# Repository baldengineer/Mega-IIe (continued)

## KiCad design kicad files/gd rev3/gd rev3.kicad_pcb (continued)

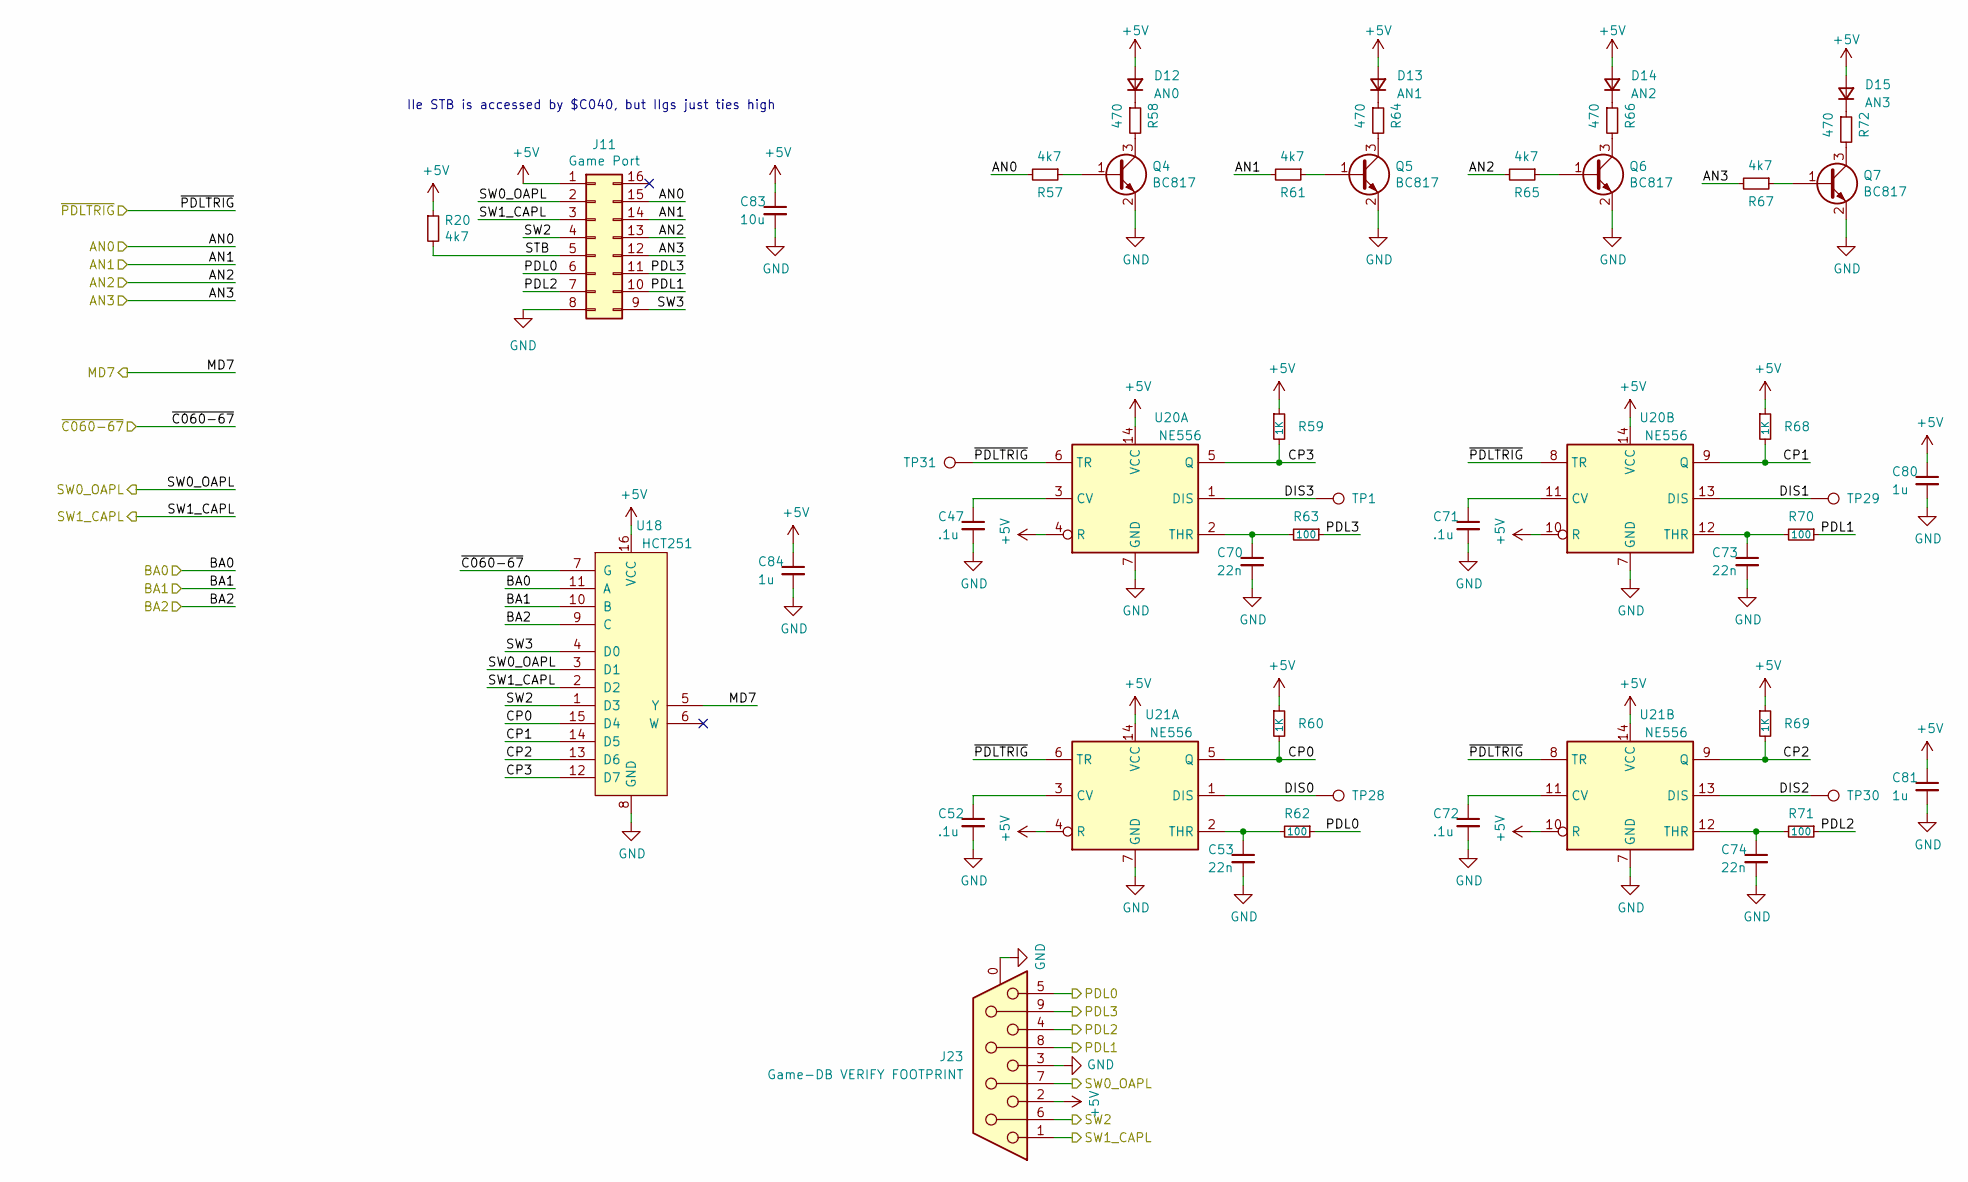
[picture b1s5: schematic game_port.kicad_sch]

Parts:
C47, C52, C71, C72: .1u; C_0805_2012Metric
C53, C70, C73, C74: 22n; C_0805_2012Metric
C80, C81, C84: 1u; C_0805_2012Metric
C83: 10u; C_0805_2012Metric
D12: AN0; LED_1206_3216Metric
D13: AN1; LED_1206_3216Metric
D14: AN2; LED_1206_3216Metric
D15: AN3; LED_1206_3216Metric
J11: Game Port; DIP-16_W7.62mm_Socket
J23: Game-DB VERIFY FOOTPRINT; DSUB-9_Female_Horizontal_P2.77x2.84mm_EdgePinOffset4.94mm_H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
Q4, Q5, Q6, Q7: BC817; SOT-23
R20, R57, R61, R65, R67: 4k7; R_0805_2012Metric
R58, R64, R66, R72: 470; R_0805_2012Metric
R59, R60, R68, R69: 1K; R_0805_2012Metric
R62, R63, R70, R71: 100; R_0805_2012Metric
TP1, TP28, TP29, TP30, TP31: TestPoint; TestPoint_Pad_D1.0mm
U18: HCT251; SOIC-16_3.9x9.9mm_P1.27mm; MPN 74HCT251D,652
U20, U21: NE556; SO-14_3.9x8.65mm_P1.27mm

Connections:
/IWM/BA0: U18.11 (A); also elsewhere on the board
/IWM/BA1: U18.10 (B); also elsewhere on the board
/IWM/BA2: U18.9 (C); also elsewhere on the board
/IWM/MD7: U18.5 (Y); also elsewhere on the board
/Slot/AN0: J11.15, R57.2; also elsewhere on the board
/Slot/AN1: J11.14, R61.2; also elsewhere on the board
/Slot/AN2: J11.13, R65.2; also elsewhere on the board
/Slot/AN3: J11.12, R67.2; also elsewhere on the board
/game_port/CP0: R60.2, U18.15 (D4), U21.5 (Q)
/game_port/CP1: R68.2, U18.14 (D5), U20.9 (Q)
/game_port/CP2: R69.2, U18.13 (D6), U21.9 (Q)
/game_port/CP3: R59.2, U18.12 (D7), U20.5 (Q)
/game_port/DIS0: TP28.1, U21.1 (DIS)
/game_port/DIS1: TP29.1, U20.13 (DIS)
/game_port/DIS2: TP30.1, U21.13 (DIS)
/game_port/DIS3: TP1.1, U20.1 (DIS)
/game_port/PDL0: J11.6, J23.5, R62.1
/game_port/PDL1: J11.10, J23.8, R70.1
/game_port/PDL2: J11.7, J23.4, R71.1
/game_port/PDL3: J11.11, J23.9, R63.1
/game_port/STB: J11.5, R20.2
/game_port/SW0_OAPL: J11.2, J23.7, U18.3 (D1)
/game_port/SW1_CAPL: J11.3, J23.1, U18.2 (D2)
/game_port/SW2: J11.4, J23.6, U18.1 (D3)
/game_port/SW3: J11.9, U18.4 (D0)
/game_port/~C060-67: U18.7 (G); also elsewhere on the board
/game_port/~PDLTRIG: TP31.1, U20.6 (TR), U20.8 (TR), U21.6 (TR), U21.8 (TR); also elsewhere on the board
GND: C47.2, C52.2, C53.2, C70.2, C71.2, C72.2, C73.2, C74.2, C80.2, C81.2, C83.2, C84.2, J11.8, J23.0 (PAD), J23.3, Q4.2 (E), Q5.2 (E), Q6.2 (E), Q7.2 (E), U18.8 (GND), U20.7 (GND), U21.7 (GND); also elsewhere on the board
unnamed: C47.1, U20.3 (CV)
unnamed: C52.1, U21.3 (CV)
unnamed: C53.1, R62.2, U21.2 (THR)
unnamed: C70.1, R63.2, U20.2 (THR)
unnamed: C71.1, U20.11 (CV)
unnamed: C72.1, U21.11 (CV)
unnamed: C73.1, R70.2, U20.12 (THR)
unnamed: C74.1, R71.2, U21.12 (THR)
unnamed: D12.1 (K), R58.1
unnamed: D13.1 (K), R64.1
unnamed: D14.1 (K), R66.1
unnamed: D15.1 (K), R72.1
unnamed: Q4.1 (B), R57.1
unnamed: Q4.3 (C), R58.2
unnamed: Q5.1 (B), R61.1
unnamed: Q5.3 (C), R64.2
unnamed: Q6.1 (B), R65.1
unnamed: Q6.3 (C), R66.2
unnamed: Q7.1 (B), R67.1
unnamed: Q7.3 (C), R72.2

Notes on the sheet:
IIe STB is accessed by $C040, but IIgs just ties high

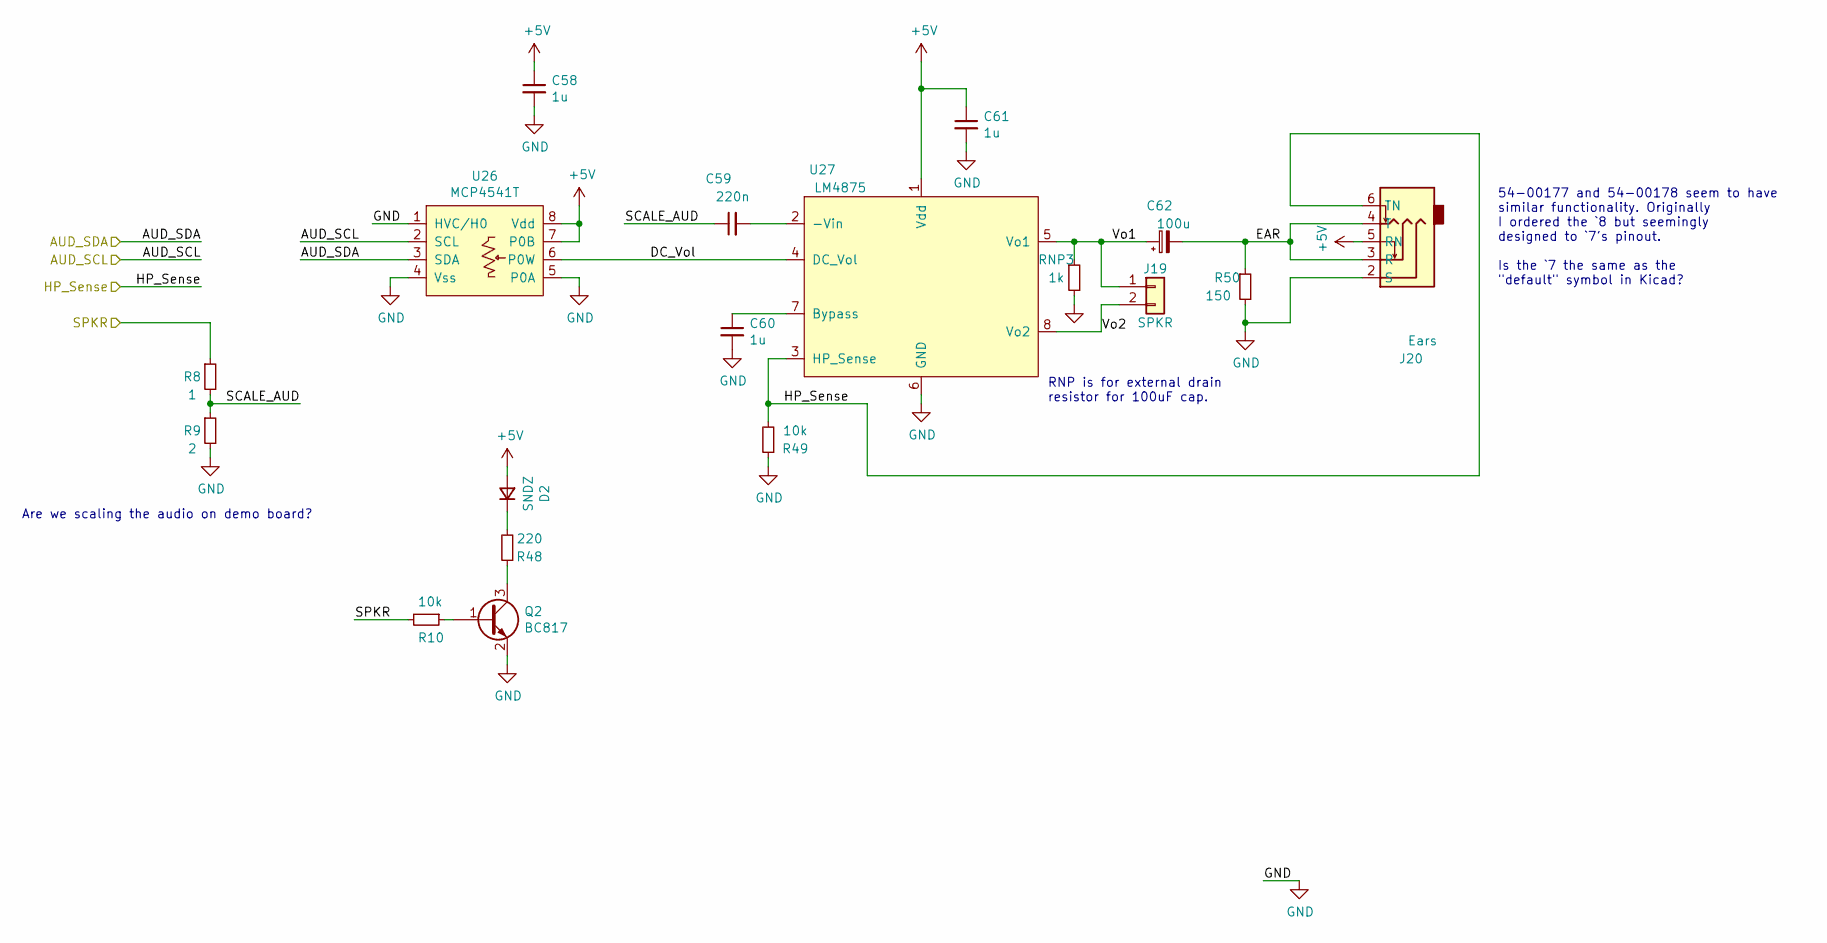
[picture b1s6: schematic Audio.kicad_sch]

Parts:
C58, C60, C61: 1u; R_0805_2012Metric
C59: 220n; R_1206_3216Metric
C62: 100u; CP_EIA-3216-18_Kemet-A; MPN T520A107M006ATE035
D2: SNDZ; LED_1206_3216Metric
J19: SPKR; PinHeader_1x02_P2.54mm_Vertical
J20: Ears; Jack_3.5mm_tensility_54-00177; MPN 54-00178
Q2: BC817; SOT-23
R8: 1; R_0805_2012Metric
R9: 2; R_0805_2012Metric
R10, R49: 10k; R_0805_2012Metric
R48: 220; R_0805_2012Metric
R50: 150; R_0805_2012Metric
RNP3: 1k; R_0805_2012Metric
U26: MCP4541T; MSOP-8_3x3mm_P0.65mm
U27: LM4875; SOIC-8_3.9x4.9mm_P1.27mm

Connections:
/Audio/AUD_SCL: U26.2 (SCL)
/Audio/AUD_SDA: U26.3 (SDA)
/Audio/DC_Vol: U26.6 (P0W), U27.4 (DC_Vol)
/Audio/EAR: C62.2, J20.3 (R), J20.4 (T), R50.1
/Audio/HP_Sense: J20.6 (TN), R49.2, U27.3 (HP_Sense)
/Audio/SCALE_AUD: C59.1, R8.2, R9.1
/Audio/SPKR: R8.1, R10.2; also elsewhere on the board
/Audio/Vo1: C62.1, J19.1, RNP3.1, U27.5 (Vo1)
/Audio/Vo2: J19.2, U27.8 (Vo2)
GND: C58.2, C60.2, C61.2, J20.2 (S), Q2.2 (E), R9.2, R49.1, R50.2, RNP3.2, U26.1 (HVC/H0), U26.4 (Vss), U26.5 (P0A), U27.6 (GND); also elsewhere on the board
unnamed: C59.2, U27.2 (-Vin)
unnamed: C60.1, U27.7 (Bypass)
unnamed: D2.1 (K), R48.2
unnamed: Q2.1 (B), R10.1
unnamed: Q2.3 (C), R48.1

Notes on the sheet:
Are we scaling the audio on demo board?
RNP is for external drain resistor for 100uF cap.
54-00177 and 54-00178 seem to have similar functionality. Originally I ordered the `8 but seemingly designed to `7's pinout. Is the `7 the same as the "default" symbol in Kicad?

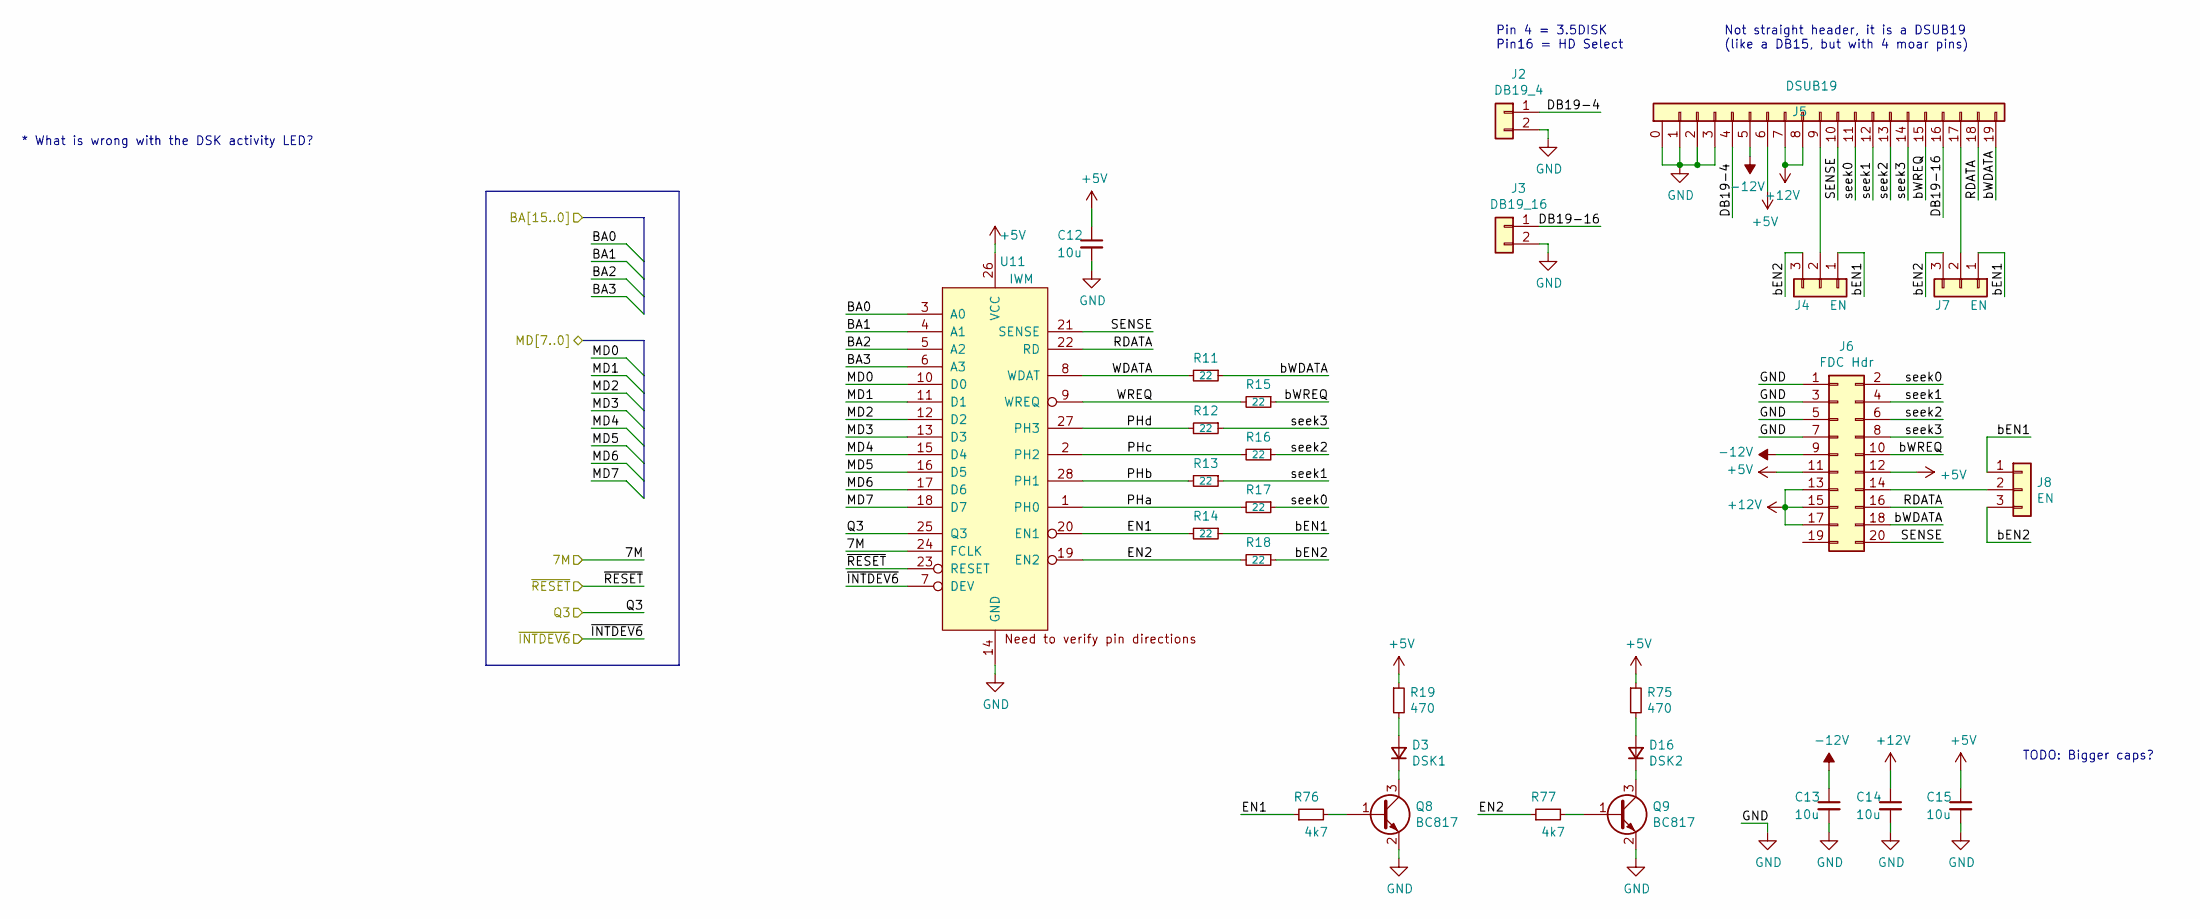
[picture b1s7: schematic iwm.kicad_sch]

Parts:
C12, C13, C14, C15: 10u; C_0805_2012Metric
D3: DSK1; LED_1206_3216Metric
D16: DSK2; LED_1206_3216Metric
J2: DB19_4; PinHeader_1x02_P2.54mm_Vertical-LOCK
J3: DB19_16; PinHeader_1x02_P2.54mm_Vertical-LOCK
J4, J7, J8: EN; PinHeader_1x03_P2.54mm_Vertical-LOCK
J5: DSUB19; DSUB-19_Apple_II_Floppy
J6: FDC Hdr; PinHeader_2x10_P2.54mm_Vertical
Q8, Q9: BC817; SOT-23
R11, R12, R13, R14, R15, R16, R17, R18: 22; R_0805_2012Metric
R19, R75: 470; R_0805_2012Metric
R76, R77: 4k7; R_0805_2012Metric
U11: IWM; PLCC-28_THT-Socket

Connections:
+12V: C14.1, J5.7, J5.8, J6.13, J6.15, J6.17; also elsewhere on the board
-12V: C13.1, J5.5, J6.9; also elsewhere on the board
/IWM/7M: U11.24 (FCLK); also elsewhere on the board
/IWM/BA0: U11.3 (A0); also elsewhere on the board
/IWM/BA1: U11.4 (A1); also elsewhere on the board
/IWM/BA2: U11.5 (A2); also elsewhere on the board
/IWM/BA3: U11.6 (A3); also elsewhere on the board
/IWM/DB19-4: J2.1, J5.4
/IWM/DB19-16: J3.1, J5.16
/IWM/EN1: R14.2, R76.1, U11.20 (EN1)
/IWM/EN2: R18.2, R77.1, U11.19 (EN2)
/IWM/MD0: U11.10 (D0); also elsewhere on the board
/IWM/MD1: U11.11 (D1); also elsewhere on the board
/IWM/MD2: U11.12 (D2); also elsewhere on the board
/IWM/MD3: U11.13 (D3); also elsewhere on the board
/IWM/MD4: U11.15 (D4); also elsewhere on the board
/IWM/MD5: U11.16 (D5); also elsewhere on the board
/IWM/MD6: U11.17 (D6); also elsewhere on the board
/IWM/MD7: U11.18 (D7); also elsewhere on the board
/IWM/PHa: R17.2, U11.1 (PH0)
/IWM/PHb: R13.2, U11.28 (PH1)
/IWM/PHc: R16.2, U11.2 (PH2)
/IWM/PHd: R12.2, U11.27 (PH3)
/IWM/Q3: U11.25 (Q3); also elsewhere on the board
/IWM/RDATA: J5.18, J6.16, U11.22 (RD)
/IWM/SENSE: J5.10, J6.20, U11.21 (SENSE)
/IWM/WDATA: R11.2, U11.8 (WDAT)
/IWM/WREQ: R15.2, U11.9 (WREQ)
/IWM/bEN1: J4.1, J7.1, J8.1, R14.1
/IWM/bEN2: J4.3, J7.3, J8.3, R18.1
/IWM/bWDATA: J5.19, J6.18, R11.1
/IWM/bWREQ: J5.15, J6.10, R15.1
/IWM/seek0: J5.11, J6.2, R17.1
/IWM/seek1: J5.12, J6.4, R13.1
/IWM/seek2: J5.13, J6.6, R16.1
/IWM/seek3: J5.14, J6.8, R12.1
/IWM/~INTDEV6: U11.7 (DEV); also elsewhere on the board
/IWM/~RESET: U11.23 (RESET); also elsewhere on the board
GND: C12.2, C13.2, C14.2, C15.2, J2.2, J3.2, J5.0, J5.1, J5.2, J5.3, J6.1, J6.3, J6.5, J6.7, Q8.2 (E), Q9.2 (E), U11.14 (GND); also elsewhere on the board
unnamed: D3.1 (K), Q8.3 (C)
unnamed: D3.2 (A), R19.2
unnamed: D16.1 (K), Q9.3 (C)
unnamed: D16.2 (A), R75.2
unnamed: J4.2, J5.9
unnamed: J5.17, J7.2
unnamed: J6.14, J8.2
unnamed: Q8.1 (B), R76.2
unnamed: Q9.1 (B), R77.2

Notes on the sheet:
* What is wrong with the DSK activity LED?
Not straight header, it is a DSUB19 (like a DB15, but with 4 moar pins)
TODO: Bigger caps?
Pin 4 = 3.5DISK Pin16 = HD Select

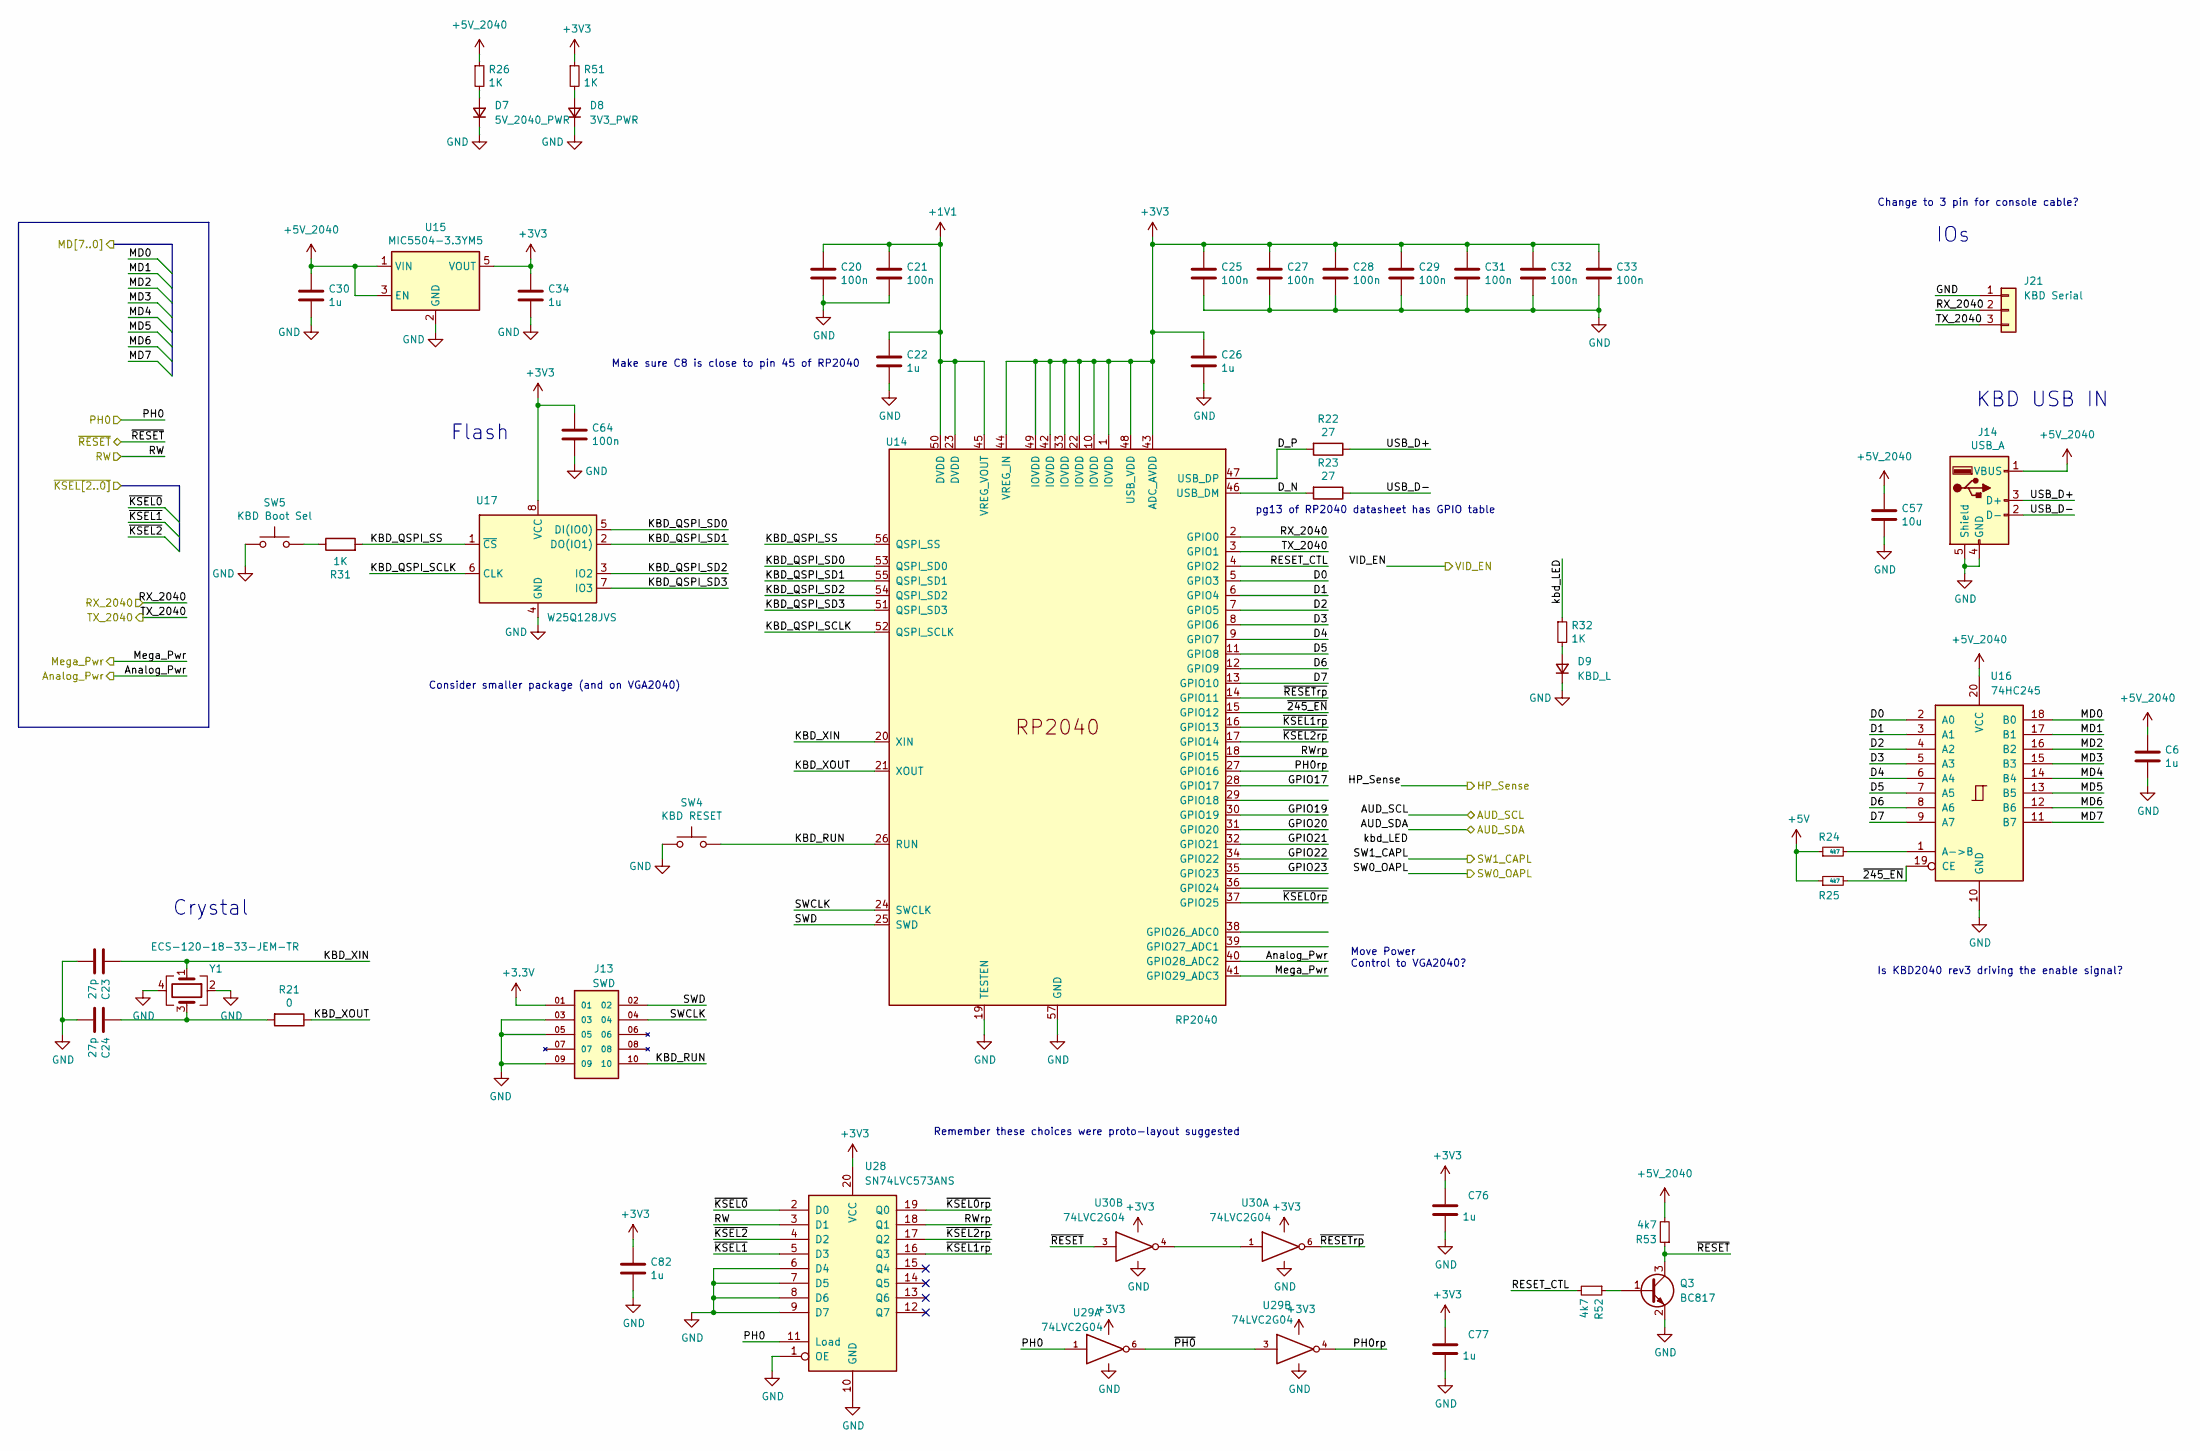
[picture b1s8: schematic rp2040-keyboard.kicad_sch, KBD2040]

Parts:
C6, C30, C34: 1u; C_0805_2012Metric
C20, C21, C25, C27, C28, C29, C31, C32, C33: 100n; C_0603_1608Metric
C22, C26, C76, C77, C82: 1u; C_0603_1608Metric
C23, C24: 27p; C_0603_1608Metric
C57: 10u; C_0805_2012Metric
C64: 100n; C_0805_2012Metric
D7: 5V_2040_PWR; LED_1206_3216Metric
D8: 3V3_PWR; LED_1206_3216Metric
D9: KBD_L; LED_1206_3216Metric
J13: SWD; SAMTEC_FTSH-105-XX-X-DV; PARTREV H
J14: USB_A; USB_A_GCT_USB1125; MPN USB1125-GF-B
J21: KBD Serial; PinSocket_1x03_P2.54mm_Vertical
Q3: BC817; SOT-23
R21: 0; R_0603_1608Metric
R22, R23: 27; R_0603_1608Metric
R24, R25, R52, R53: 4k7; R_0805_2012Metric
R26, R32, R51: 1K; R_0805_2012Metric
R31: 1K; R_0603_1608Metric
SW4: KBD RESET; SW_SPST_PTS810
SW5: KBD Boot Sel; SW_SPST_PTS810
U14: RP2040; RP2040-QFN-56
U15: MIC5504-3.3YM5; SOT-23-5
U16: 74HC245; SO-20_5.3x12.6mm_P1.27mm
U17: W25Q128JVS; SOIC-8_5.23x5.23mm_P1.27mm
U28: SN74LVC573ANS; SO-20_5.3x12.6mm_P1.27mm
U29, U30: 74LVC2G04; SOT-23-6
Y1: ECS-120-18-33-JEM-TR; Crystal_SMD_3225-4Pin_3.2x2.5mm

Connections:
+1V1: C20.1, C21.1, C22.1, U14.23 (DVDD), U14.45 (VREG_VOUT), U14.50 (DVDD); also elsewhere on the board
/IWM/MD0: U16.18 (B0); also elsewhere on the board
/IWM/MD1: U16.17 (B1); also elsewhere on the board
/IWM/MD2: U16.16 (B2); also elsewhere on the board
/IWM/MD3: U16.15 (B3); also elsewhere on the board
/IWM/MD4: U16.14 (B4); also elsewhere on the board
/IWM/MD5: U16.13 (B5); also elsewhere on the board
/IWM/MD6: U16.12 (B6); also elsewhere on the board
/IWM/MD7: U16.11 (B7); also elsewhere on the board
/IWM/~RESET: Q3.3 (C), R53.1, U30.3; also elsewhere on the board
/Slot/PH0: U28.11 (Load), U29.1; also elsewhere on the board
/Slot/RW: U28.3 (D1); also elsewhere on the board
/mega-6502/~KSEL0: U28.2 (D0); also elsewhere on the board
/mega-6502/~KSEL1: U28.5 (D3); also elsewhere on the board
/mega-6502/~KSEL2: U28.4 (D2); also elsewhere on the board
/power/Analog_Pwr: U14.40 (GPIO28_ADC2); also elsewhere on the board
/power/Mega_Pwr: U14.41 (GPIO29_ADC3); also elsewhere on the board
/rp2040-keyboard/D0: U14.5 (GPIO3), U16.2 (A0)
/rp2040-keyboard/D1: U14.6 (GPIO4), U16.3 (A1)
/rp2040-keyboard/D2: U14.7 (GPIO5), U16.4 (A2)
/rp2040-keyboard/D3: U14.8 (GPIO6), U16.5 (A3)
/rp2040-keyboard/D4: U14.9 (GPIO7), U16.6 (A4)
/rp2040-keyboard/D5: U14.11 (GPIO8), U16.7 (A5)
/rp2040-keyboard/D6: U14.12 (GPIO9), U16.8 (A6)
/rp2040-keyboard/D7: U14.13 (GPIO10), U16.9 (A7)
/rp2040-keyboard/D_N: R23.2, U14.46 (USB_DM)
/rp2040-keyboard/D_P: R22.2, U14.47 (USB_DP)
/rp2040-keyboard/GPIO17: U14.28 (GPIO17)
/rp2040-keyboard/GPIO19: U14.30 (GPIO19)
/rp2040-keyboard/GPIO20: U14.31 (GPIO20)
/rp2040-keyboard/GPIO21: U14.32 (GPIO21)
/rp2040-keyboard/GPIO22: U14.34 (GPIO22)
/rp2040-keyboard/GPIO23: U14.35 (GPIO23)
/rp2040-keyboard/KBD_QSPI_SCLK: U14.52 (QSPI_SCLK), U17.6 (CLK)
/rp2040-keyboard/KBD_QSPI_SD0: U14.53 (QSPI_SD0), U17.5 (DI(IO0))
/rp2040-keyboard/KBD_QSPI_SD1: U14.55 (QSPI_SD1), U17.2 (DO(IO1))
/rp2040-keyboard/KBD_QSPI_SD2: U14.54 (QSPI_SD2), U17.3 (IO2)
/rp2040-keyboard/KBD_QSPI_SD3: U14.51 (QSPI_SD3), U17.7 (IO3)
/rp2040-keyboard/KBD_QSPI_SS: R31.2, U14.56 (QSPI_SS), U17.1 (~CS)
/rp2040-keyboard/KBD_RUN: J13.10, SW4.2, U14.26 (RUN)
/rp2040-keyboard/KBD_XIN: C23.1, U14.20 (XIN), Y1.1
/rp2040-keyboard/KBD_XOUT: R21.1, U14.21 (XOUT)
/rp2040-keyboard/PH0rp: U14.27 (GPIO16), U29.4
/rp2040-keyboard/RESET_CTL: R52.2, U14.4 (GPIO2)
/rp2040-keyboard/RWrp: U14.18 (GPIO15), U28.18 (Q1)
/rp2040-keyboard/RX_2040: J21.2, U14.2 (GPIO0); also elsewhere on the board
/rp2040-keyboard/SWCLK: J13.04, U14.24 (SWCLK)
/rp2040-keyboard/SWD: J13.02, U14.25 (SWD)
/rp2040-keyboard/TX_2040: J21.3, U14.3 (GPIO1); also elsewhere on the board
/rp2040-keyboard/USB_D+: J14.3 (D+), R22.1
/rp2040-keyboard/USB_D-: J14.2 (D-), R23.1
/rp2040-keyboard/kbd_LED: R32.1
/rp2040-keyboard/~245_EN: R25.2, U14.15 (GPIO12), U16.19 (CE)
/rp2040-keyboard/~KSEL0rp: U14.37 (GPIO25), U28.19 (Q0)
/rp2040-keyboard/~KSEL1rp: U14.16 (GPIO13), U28.16 (Q3)
/rp2040-keyboard/~KSEL2rp: U14.17 (GPIO14), U28.17 (Q2)
/rp2040-keyboard/~PH0: U29.3, U29.6
/rp2040-keyboard/~RESETrp: U14.14 (GPIO11), U30.6
GND: C6.2, C20.2, C21.2, C22.2, C23.2, C24.2, C25.2, C26.2, C27.2, C28.2, C29.2, C30.2, C31.2, C32.2, C33.2, C34.2, C57.2, C64.2, C76.2, C77.2, C82.2, D7.1 (K), D8.1 (K), D9.1 (K), J13.03, J13.05, J13.09, J14.4 (GND), J14.5 (Shield), J21.1, Q3.2 (E), SW4.1, SW5.1, U14.19 (TESTEN), U14.57 (GND), U15.2 (GND), U16.10 (GND), U17.4 (GND), U28.1 (OE), U28.6 (D4), U28.7 (D5), U28.8 (D6), U28.9 (D7), U28.10 (GND), U29.2 (GND), U30.2 (GND), Y1.2, Y1.4; also elsewhere on the board
unnamed: C24.1, R21.2, Y1.3
unnamed: D7.2 (A), R26.2
unnamed: D8.2 (A), R51.2
unnamed: D9.2 (A), R32.2
unnamed: Q3.1 (B), R52.1
unnamed: R24.2, U16.1 (A->B)
unnamed: R31.1, SW5.2
unnamed: U30.1, U30.4

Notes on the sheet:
IOs
Change to 3 pin for console cable?
Crystal
Move Power Control to VGA2040?
Remember these choices were proto-layout suggested
pg13 of RP2040 datasheet has GPIO table
Consider smaller package (and on VGA2040)
Flash
Is KBD2040 rev3 driving the enable signal?
KBD USB IN
Make sure C8 is close to pin 45 of RP2040

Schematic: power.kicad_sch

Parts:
D4: -12v; LED_1206_3216Metric
D5: +12v; LED_1206_3216Metric
D6: Mega; LED_1206_3216Metric
D10: Stby; LED_1206_3216Metric
J12: Right Angle; TE 5650118-3 Right Angle 12 Pos Socket
J15: Rev2 Header; PinSocket_2x05_P2.54mm_Vertical
J16: RP2040 Header; PinSocket_2x03_P2.54mm_Vertical
R27, R28, R29, R30: 1K; R_0805_2012Metric

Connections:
+12V: J12.3, J15.3, J15.4; also elsewhere on the board
-12V: J12.1, J15.1, J15.2; also elsewhere on the board
/power/Analog_Pwr: J12.12, J16.1; also elsewhere on the board
/power/Mega_Pwr: J12.11, J16.2; also elsewhere on the board
/power/Neg12_Out: D4.1 (K)
/power/Pos12_Out: R28.1
GND: D5.1 (K), D6.1 (K), D10.1 (K), J12.2, J12.4, J12.6, J12.8, J15.9, J15.10, J16.3, J16.4, R27.1; also elsewhere on the board
unnamed: D4.2 (A), R27.2
unnamed: D5.2 (A), R28.2
unnamed: D6.2 (A), R29.2
unnamed: D10.2 (A), R30.2

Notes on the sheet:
Change to SMD Package (if you can buy it)
TODO: Add filtering and some lytics.
Change PWR Control Signals to Match Mega_EN Analog_EN

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
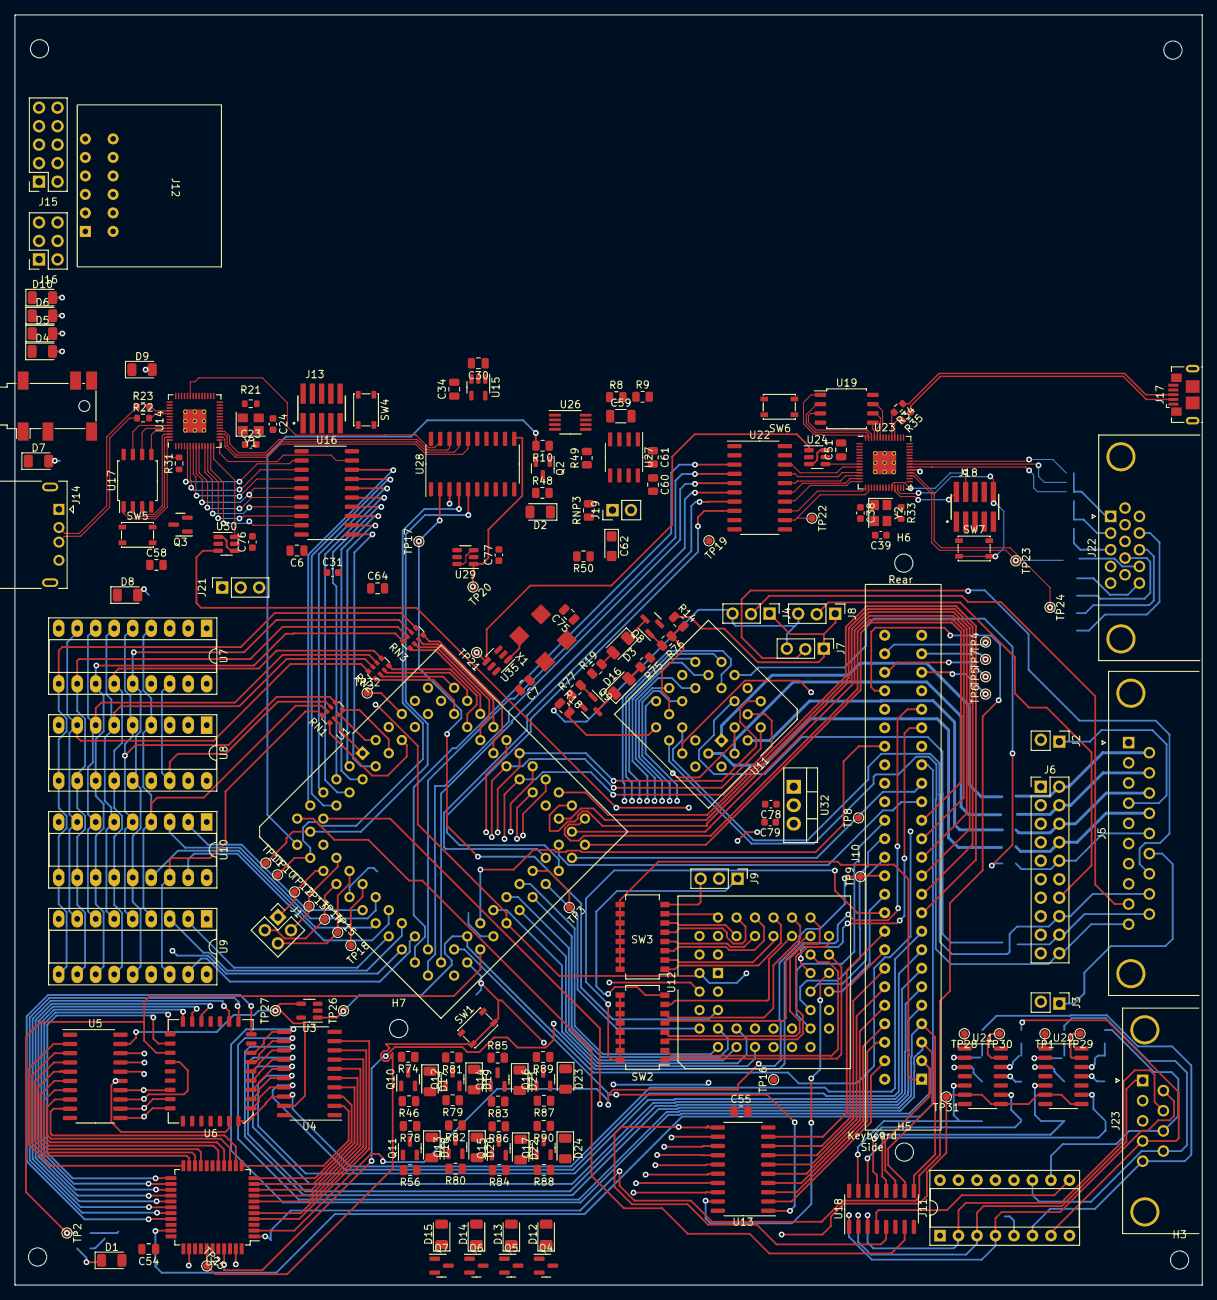
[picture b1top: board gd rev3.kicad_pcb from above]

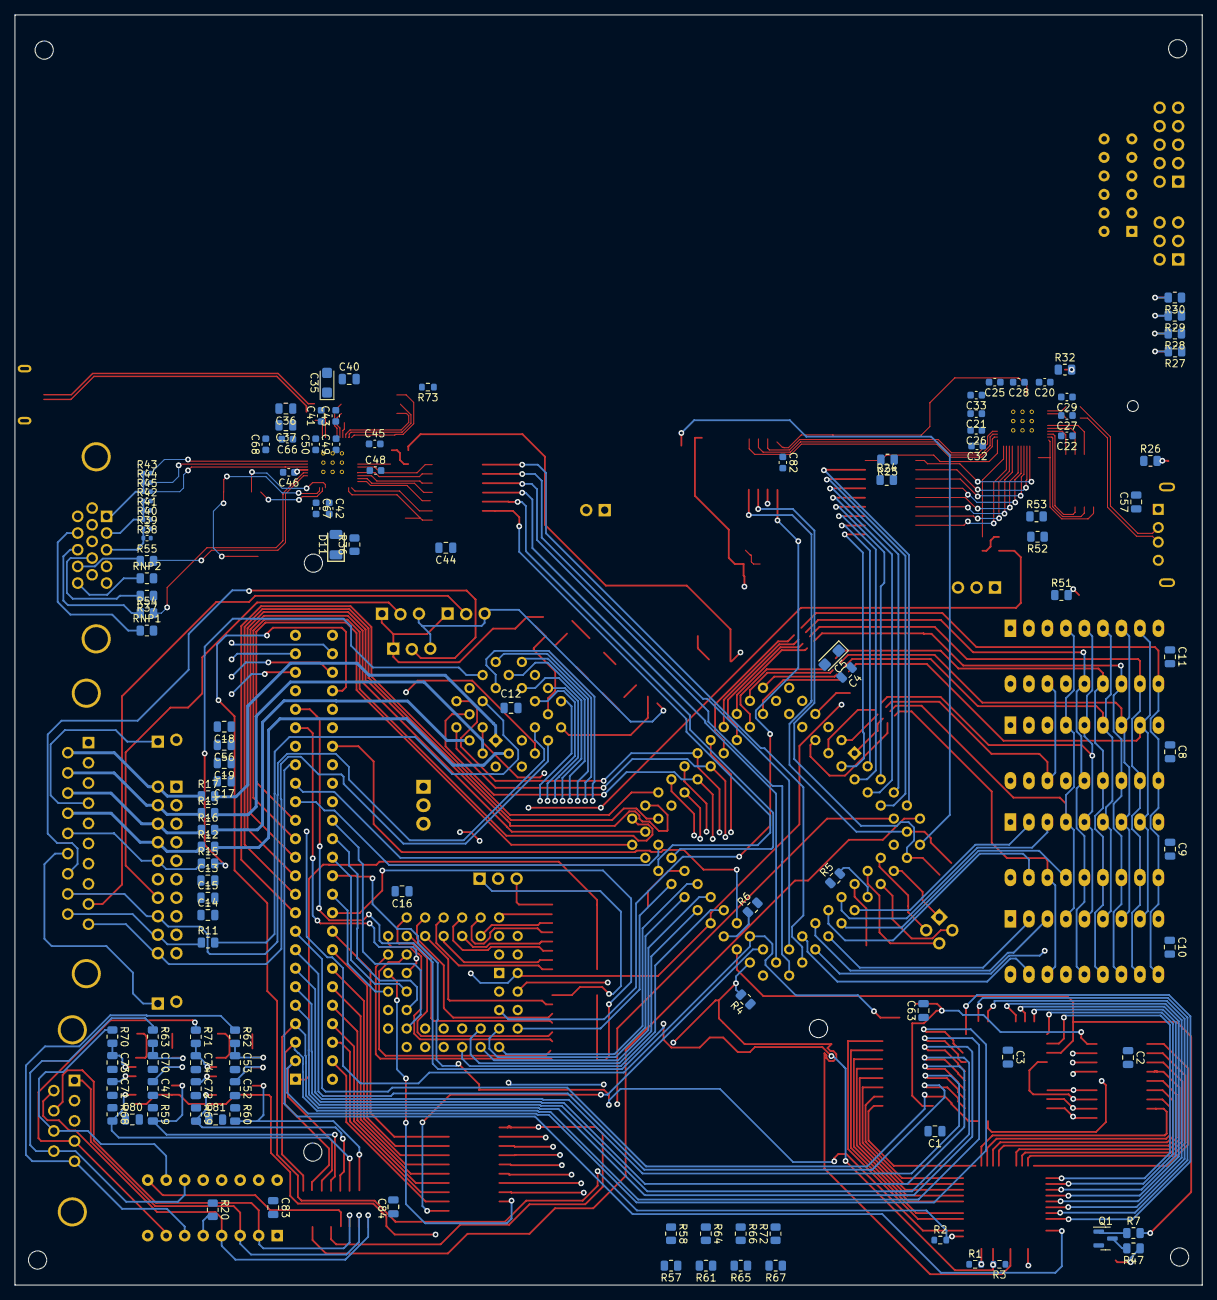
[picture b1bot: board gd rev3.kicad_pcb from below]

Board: 4 copper layers, 163.0 x 174.4 mm, 322 parts (118 on the bottom side), 364 nets.
